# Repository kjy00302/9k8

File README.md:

# Quail 9008 EDL adapter

[California Quail](https://flickr.com/photos/54430347@N04/9405494428) by USFWS Pacific Southwest Region

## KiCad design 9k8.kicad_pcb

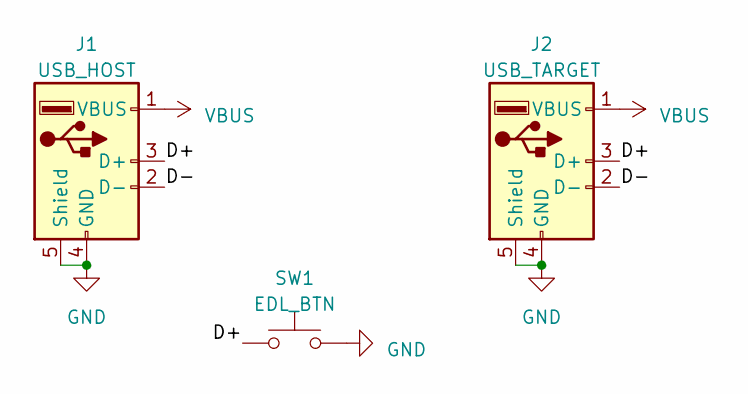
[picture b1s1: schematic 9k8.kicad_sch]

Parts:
J1: USB_HOST; USB_B_Lumberg_2411_02_Horizontal
J2: USB_TARGET; USB_A_CONNFLY_DS1095-WNR0
SW1: EDL_BTN; SW_PUSH-12mm

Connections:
/D+: J1.3 (D+), J2.3 (D+), SW1.1
/D-: J1.2 (D-), J2.2 (D-)
GND: J1.4 (GND), J1.5 (Shield), J2.4 (GND), J2.5 (Shield), SW1.2
VBUS: J1.1 (VBUS), J2.1 (VBUS)

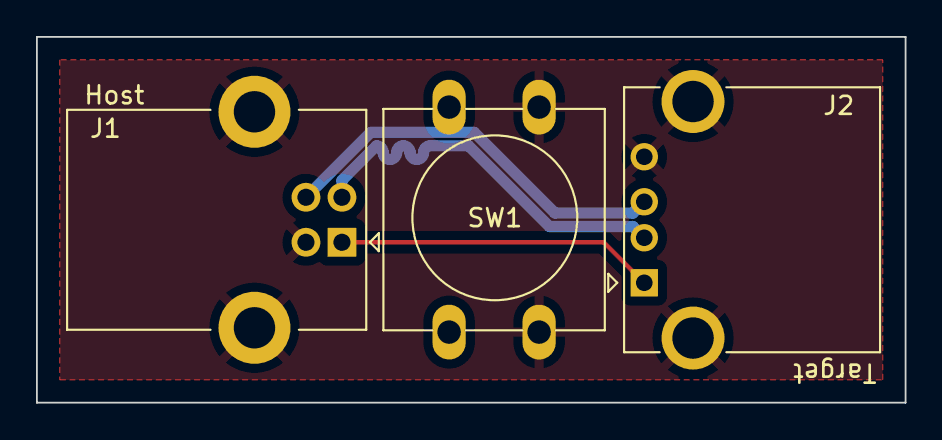
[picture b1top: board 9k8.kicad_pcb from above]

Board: 2 copper layers, 48.3 x 20.3 mm, 3 parts (0 on the bottom side), 4 nets.

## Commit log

2023-10-04 Create LICENSE
